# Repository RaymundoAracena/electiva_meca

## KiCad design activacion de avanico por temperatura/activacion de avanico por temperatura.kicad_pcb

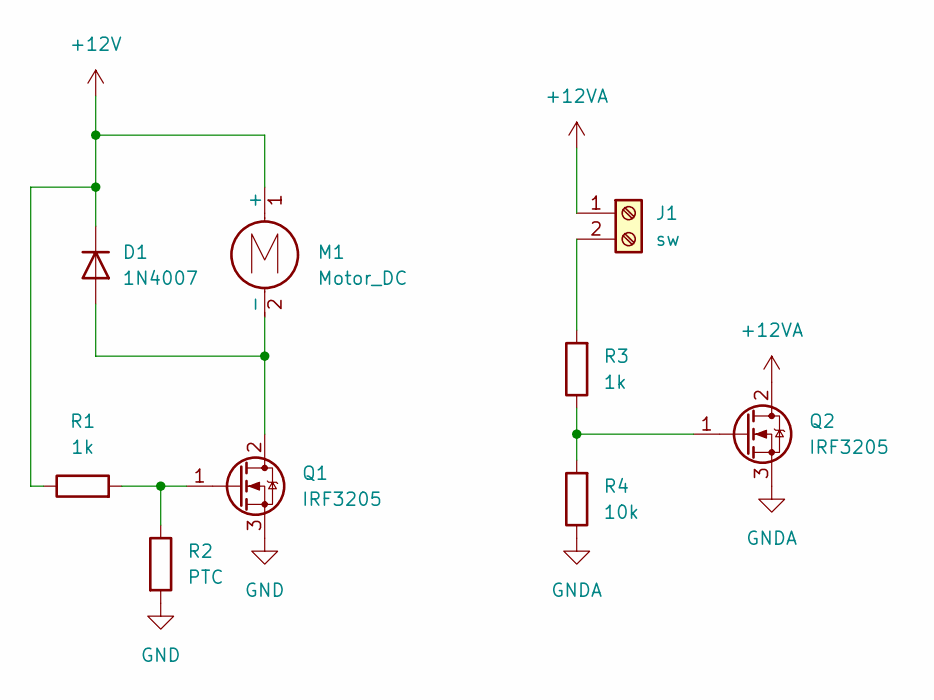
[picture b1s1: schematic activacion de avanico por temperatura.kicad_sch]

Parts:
D1: 1N4007; D_DO-41_SOD81_P10.16mm_Horizontal
J1: sw; PinHeader_1x02_P2.54mm_Vertical
M1: Motor_DC; PinHeader_1x02_P2.54mm_Vertical
Q1, Q2: IRF3205; TO-220-3_Vertical
R1, R3: 1k; R_Axial_DIN0207_L6.3mm_D2.5mm_P7.62mm_Horizontal
R2: PTC; R_Axial_DIN0204_L3.6mm_D1.6mm_P5.08mm_Horizontal
R4: 10k; R_Axial_DIN0207_L6.3mm_D2.5mm_P7.62mm_Horizontal

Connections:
+12V: D1.1 (K), M1.1 (+), R1.1
+12VA: J1.1, Q2.2 (D)
GND: Q1.3 (S), R2.2
GNDA: Q2.3 (S), R4.1
unnamed: D1.2 (A), M1.2 (-), Q1.2 (D)
unnamed: J1.2, R3.2
unnamed: Q1.1 (G), R1.2, R2.1
unnamed: Q2.1 (G), R3.1, R4.2

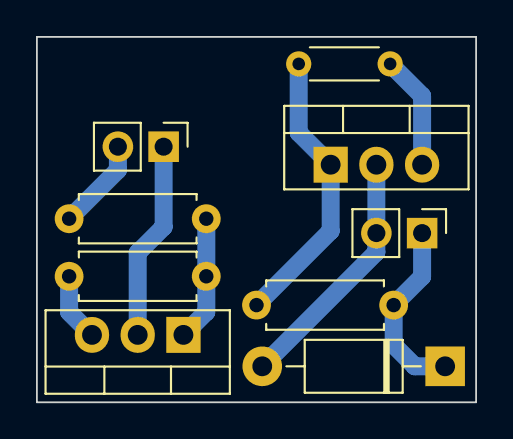
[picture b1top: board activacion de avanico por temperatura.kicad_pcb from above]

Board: 2 copper layers, 24.4 x 20.3 mm, 9 parts (0 on the bottom side), 8 nets.

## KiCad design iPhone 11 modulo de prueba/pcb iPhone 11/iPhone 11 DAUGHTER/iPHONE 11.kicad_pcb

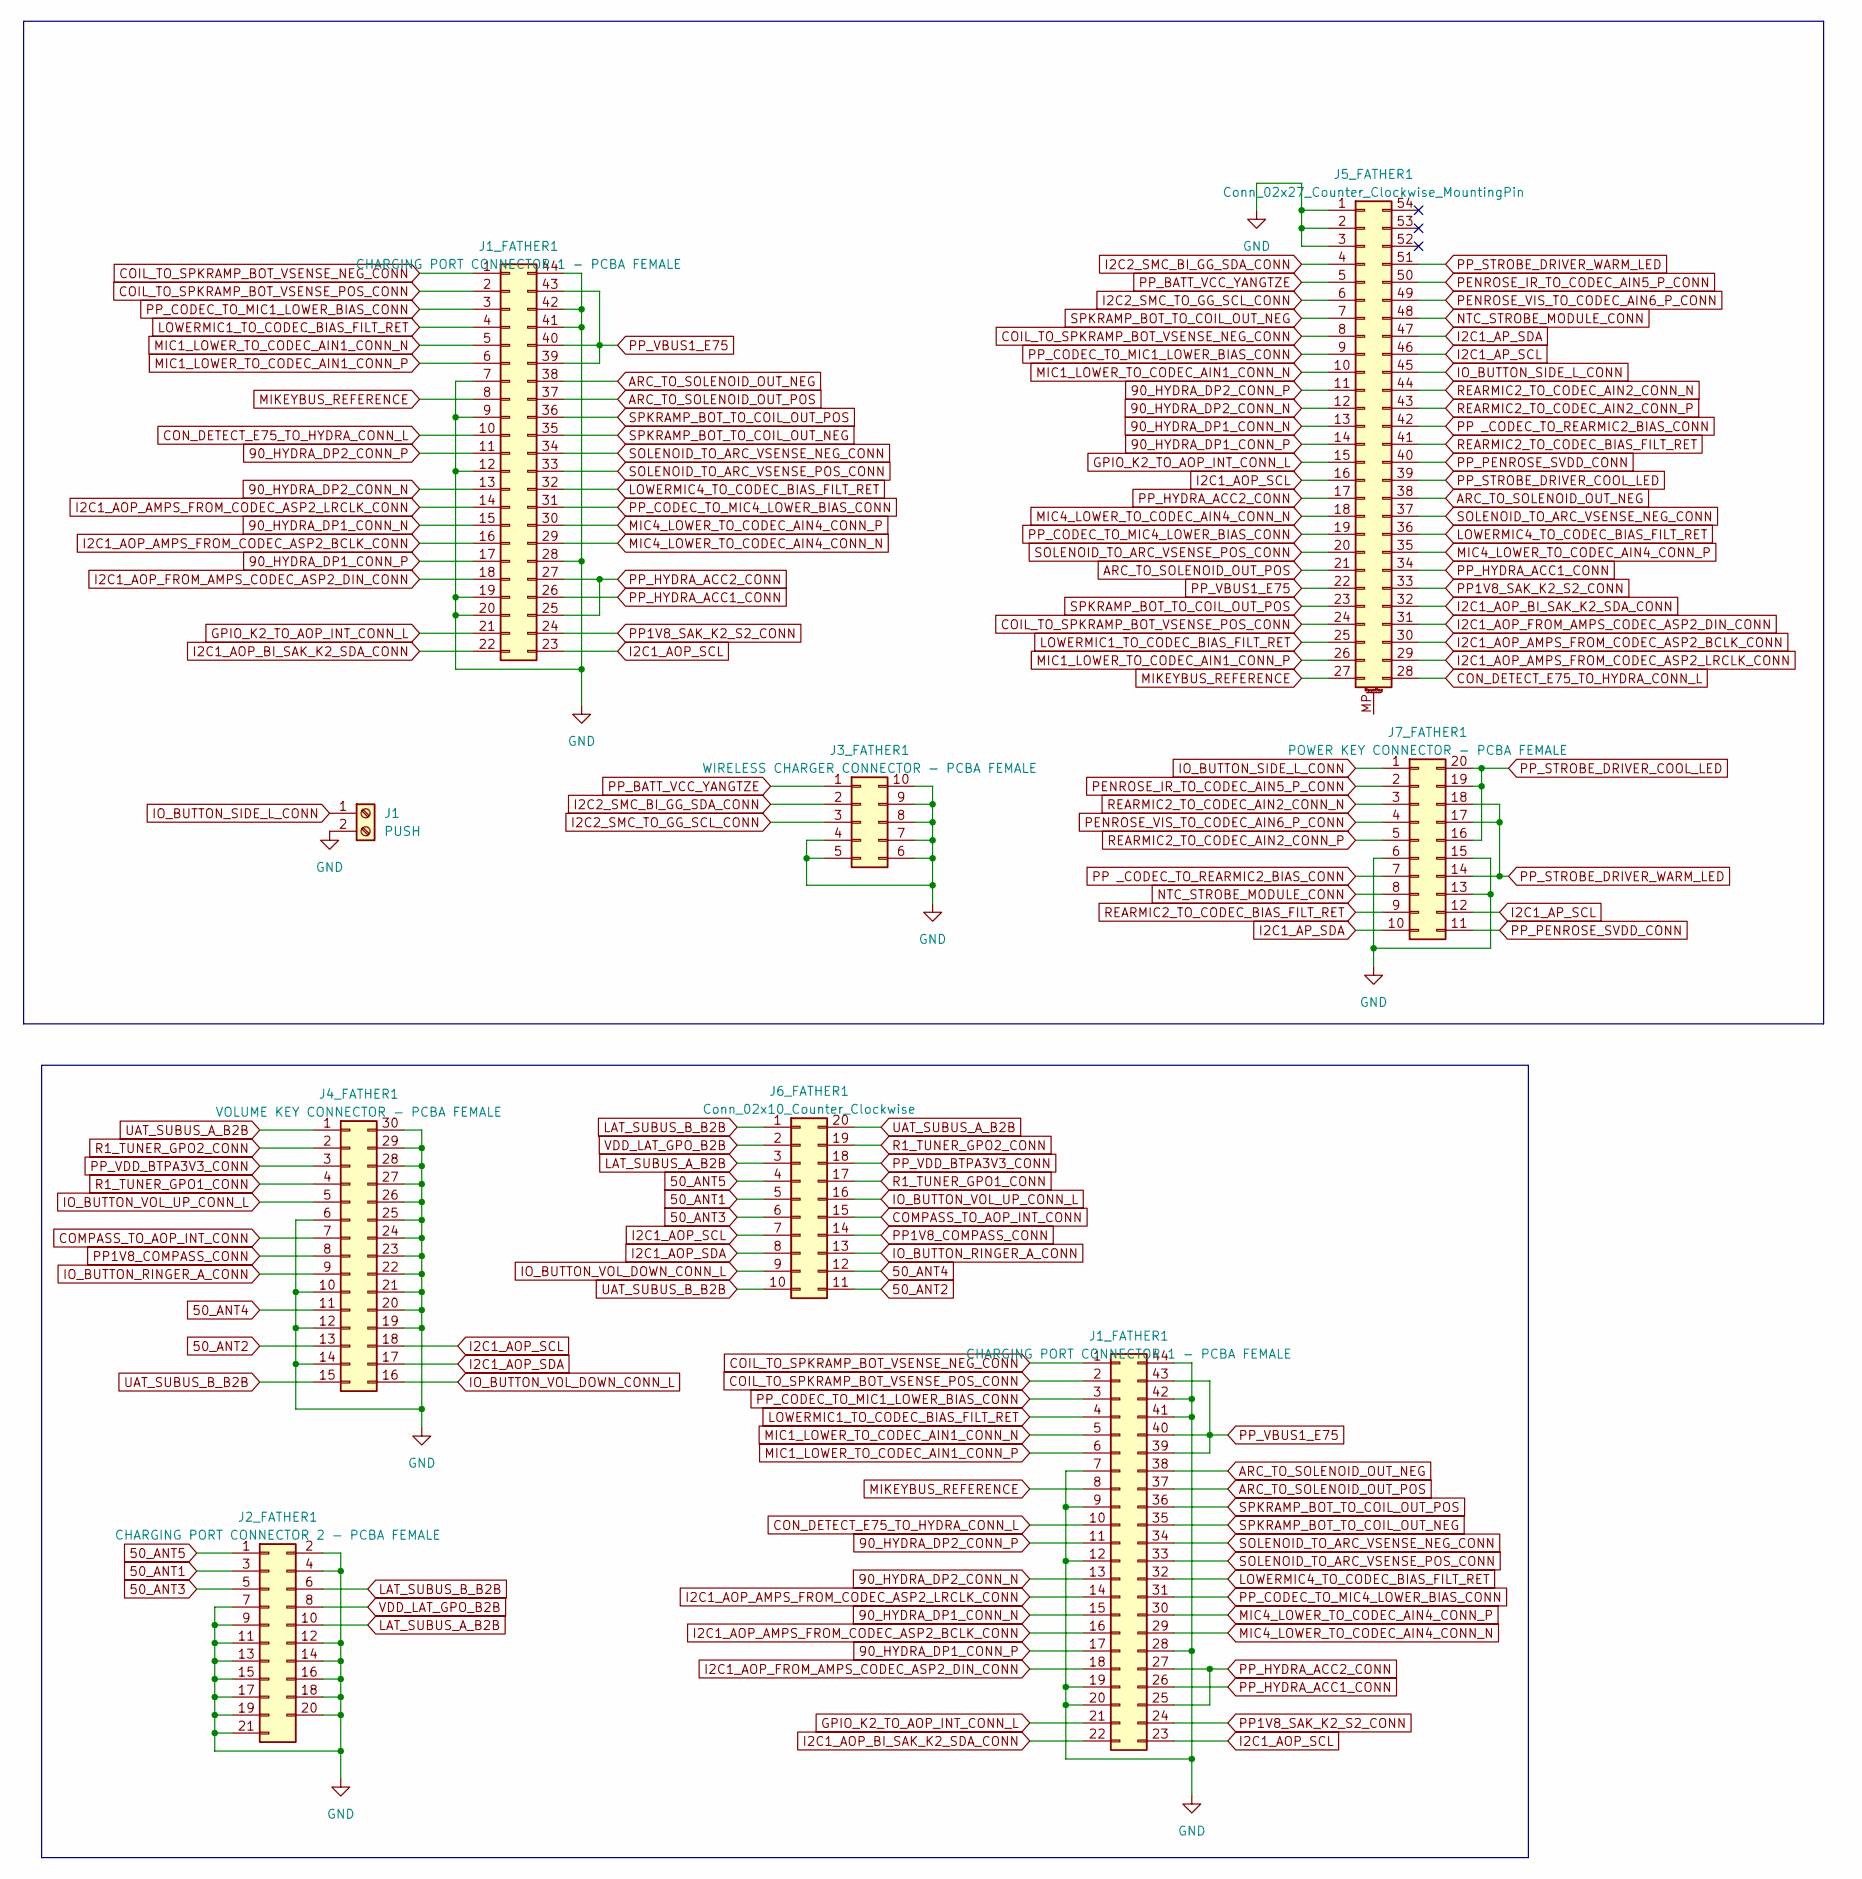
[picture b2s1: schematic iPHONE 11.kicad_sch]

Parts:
J1: PUSH; PinHeader_1x02_P2.54mm_Horizontal
J1_FATHER1: CHARGING PORT CONNECTOR 1 - PCBA FEMALE; IP11_J8200_13_PCBA_CHARGING_CONNECTOR_1
J2_FATHER1: CHARGING PORT CONNECTOR 2 - PCBA FEMALE; IP11_J-LAT-K_14_PCBA_CHARGING_CONNECTOR_2
J3_FATHER1: WIRELESS CHARGER CONNECTOR - PCBA FEMALE; IP11_J7100_7_PCBA_WIRELESS_CHARGER_CONNECTOR
J4_FATHER1: VOLUME KEY CONNECTOR - PCBA FEMALE; IP11_J-UAT-K_1_PCBA_VOLUME_KEY_CONNECTOR
J5_FATHER1: Conn_02x27_Counter_Clockwise_MountingPin; ZIF 54pin
J6_FATHER1: Conn_02x10_Counter_Clockwise; ZIF 20pin
J7_FATHER1: POWER KEY CONNECTOR - PCBA FEMALE; IP11_J7700_9_PCBA_POWER_KEY_FLEX_CONNECTOR

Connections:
50_ANT1: J2_FATHER1.3, J6_FATHER1.5
50_ANT2: J4_FATHER1.13, J6_FATHER1.11
50_ANT3: J2_FATHER1.5, J6_FATHER1.6
50_ANT4: J4_FATHER1.11, J6_FATHER1.12
50_ANT5: J2_FATHER1.1, J6_FATHER1.4
90_HYDRA_DP1_CONN_N: J1_FATHER1.15, J5_FATHER1.13; also elsewhere on the board
90_HYDRA_DP1_CONN_P: J1_FATHER1.17, J5_FATHER1.14; also elsewhere on the board
90_HYDRA_DP2_CONN_N: J1_FATHER1.13, J5_FATHER1.12; also elsewhere on the board
90_HYDRA_DP2_CONN_P: J1_FATHER1.11, J5_FATHER1.11; also elsewhere on the board
ARC_TO_SOLENOID_OUT_NEG: J1_FATHER1.38, J5_FATHER1.38; also elsewhere on the board
ARC_TO_SOLENOID_OUT_POS: J1_FATHER1.37, J5_FATHER1.21; also elsewhere on the board
COIL_TO_SPKRAMP_BOT_VSENSE_NEG_CONN: J1_FATHER1.1, J5_FATHER1.8; also elsewhere on the board
COIL_TO_SPKRAMP_BOT_VSENSE_POS_CONN: J1_FATHER1.2, J5_FATHER1.24; also elsewhere on the board
COMPASS_TO_AOP_INT_CONN: J4_FATHER1.7, J6_FATHER1.15
CON_DETECT_E75_TO_HYDRA_CONN_L: J1_FATHER1.10, J5_FATHER1.28; also elsewhere on the board
GND: J1.2, J1_FATHER1.7, J1_FATHER1.9, J1_FATHER1.12, J1_FATHER1.19, J1_FATHER1.20, J1_FATHER1.28, J1_FATHER1.41, J1_FATHER1.42, J1_FATHER1.44, J2_FATHER1.2, J2_FATHER1.4, J2_FATHER1.7, J2_FATHER1.9, J2_FATHER1.11, J2_FATHER1.12, J2_FATHER1.13, J2_FATHER1.14, J2_FATHER1.15, J2_FATHER1.16, J2_FATHER1.17, J2_FATHER1.18, J2_FATHER1.19, J2_FATHER1.20, J2_FATHER1.21, J3_FATHER1.4, J3_FATHER1.5, J3_FATHER1.6, J3_FATHER1.7, J3_FATHER1.8, J3_FATHER1.9, J3_FATHER1.10, J4_FATHER1.6, J4_FATHER1.10, J4_FATHER1.12, J4_FATHER1.14, J4_FATHER1.19, J4_FATHER1.20, J4_FATHER1.21, J4_FATHER1.22, J4_FATHER1.23, J4_FATHER1.24, J4_FATHER1.25, J4_FATHER1.26, J4_FATHER1.27, J4_FATHER1.28, J4_FATHER1.29, J4_FATHER1.30, J5_FATHER1.1, J5_FATHER1.2, J5_FATHER1.3, J7_FATHER1.6, J7_FATHER1.13, J7_FATHER1.15; also elsewhere on the board
GPIO_K2_TO_AOP_INT_CONN_L: J1_FATHER1.21, J5_FATHER1.15; also elsewhere on the board
I2C1_AOP_AMPS_FROM_CODEC_ASP2_BCLK_CONN: J1_FATHER1.16, J5_FATHER1.30; also elsewhere on the board
I2C1_AOP_AMPS_FROM_CODEC_ASP2_LRCLK_CONN: J1_FATHER1.14, J5_FATHER1.29; also elsewhere on the board
I2C1_AOP_BI_SAK_K2_SDA_CONN: J1_FATHER1.22, J5_FATHER1.32; also elsewhere on the board
I2C1_AOP_FROM_AMPS_CODEC_ASP2_DIN_CONN: J1_FATHER1.18, J5_FATHER1.31; also elsewhere on the board
I2C1_AOP_SCL: J1_FATHER1.23, J4_FATHER1.18, J5_FATHER1.16, J6_FATHER1.7; also elsewhere on the board
I2C1_AOP_SDA: J4_FATHER1.17, J6_FATHER1.8
I2C1_AP_SCL: J5_FATHER1.46, J7_FATHER1.12
I2C1_AP_SDA: J5_FATHER1.47, J7_FATHER1.10
I2C2_SMC_BI_GG_SDA_CONN: J3_FATHER1.2, J5_FATHER1.4
I2C2_SMC_TO_GG_SCL_CONN: J3_FATHER1.3, J5_FATHER1.6
IO_BUTTON_RINGER_A_CONN: J4_FATHER1.9, J6_FATHER1.13
IO_BUTTON_SIDE_L_CONN: J1.1, J5_FATHER1.45, J7_FATHER1.1
IO_BUTTON_VOL_DOWN_CONN_L: J4_FATHER1.16, J6_FATHER1.9
IO_BUTTON_VOL_UP_CONN_L: J4_FATHER1.5, J6_FATHER1.16
LAT_SUBUS_A_B2B: J2_FATHER1.10, J6_FATHER1.3
LAT_SUBUS_B_B2B: J2_FATHER1.6, J6_FATHER1.1
LOWERMIC1_TO_CODEC_BIAS_FILT_RET: J1_FATHER1.4, J5_FATHER1.25; also elsewhere on the board
LOWERMIC4_TO_CODEC_BIAS_FILT_RET: J1_FATHER1.32, J5_FATHER1.36; also elsewhere on the board
MIC1_LOWER_TO_CODEC_AIN1_CONN_N: J1_FATHER1.5, J5_FATHER1.10; also elsewhere on the board
MIC1_LOWER_TO_CODEC_AIN1_CONN_P: J1_FATHER1.6, J5_FATHER1.26; also elsewhere on the board
MIC4_LOWER_TO_CODEC_AIN4_CONN_N: J1_FATHER1.29, J5_FATHER1.18; also elsewhere on the board
MIC4_LOWER_TO_CODEC_AIN4_CONN_P: J1_FATHER1.30, J5_FATHER1.35; also elsewhere on the board
MIKEYBUS_REFERENCE: J1_FATHER1.8, J5_FATHER1.27; also elsewhere on the board
NTC_STROBE_MODULE_CONN: J5_FATHER1.48, J7_FATHER1.8
PENROSE_IR_TO_CODEC_AIN5_P_CONN: J5_FATHER1.50, J7_FATHER1.2
PENROSE_VIS_TO_CODEC_AIN6_P_CONN: J5_FATHER1.49, J7_FATHER1.4
PP1V8_COMPASS_CONN: J4_FATHER1.8, J6_FATHER1.14
PP1V8_SAK_K2_S2_CONN: J1_FATHER1.24, J5_FATHER1.33; also elsewhere on the board
PP _CODEC_TO_REARMIC2_BIAS_CONN: J5_FATHER1.42, J7_FATHER1.7
PP_BATT_VCC_YANGTZE: J3_FATHER1.1, J5_FATHER1.5
PP_CODEC_TO_MIC1_LOWER_BIAS_CONN: J1_FATHER1.3, J5_FATHER1.9; also elsewhere on the board
PP_CODEC_TO_MIC4_LOWER_BIAS_CONN: J1_FATHER1.31, J5_FATHER1.19; also elsewhere on the board
PP_HYDRA_ACC1_CONN: J1_FATHER1.26, J5_FATHER1.34; also elsewhere on the board
PP_HYDRA_ACC2_CONN: J1_FATHER1.25, J1_FATHER1.27, J5_FATHER1.17; also elsewhere on the board
PP_PENROSE_SVDD_CONN: J5_FATHER1.40, J7_FATHER1.11
PP_STROBE_DRIVER_COOL_LED: J5_FATHER1.39, J7_FATHER1.16, J7_FATHER1.19, J7_FATHER1.20
PP_STROBE_DRIVER_WARM_LED: J5_FATHER1.51, J7_FATHER1.14, J7_FATHER1.17, J7_FATHER1.18
PP_VBUS1_E75: J1_FATHER1.39, J1_FATHER1.40, J1_FATHER1.43, J5_FATHER1.22; also elsewhere on the board
PP_VDD_BTPA3V3_CONN: J4_FATHER1.3, J6_FATHER1.18
R1_TUNER_GPO1_CONN: J4_FATHER1.4, J6_FATHER1.17
R1_TUNER_GPO2_CONN: J4_FATHER1.2, J6_FATHER1.19
REARMIC2_TO_CODEC_AIN2_CONN_N: J5_FATHER1.44, J7_FATHER1.3
REARMIC2_TO_CODEC_AIN2_CONN_P: J5_FATHER1.43, J7_FATHER1.5
REARMIC2_TO_CODEC_BIAS_FILT_RET: J5_FATHER1.41, J7_FATHER1.9
SOLENOID_TO_ARC_VSENSE_NEG_CONN: J1_FATHER1.34, J5_FATHER1.37; also elsewhere on the board
SOLENOID_TO_ARC_VSENSE_POS_CONN: J1_FATHER1.33, J5_FATHER1.20; also elsewhere on the board
SPKRAMP_BOT_TO_COIL_OUT_NEG: J1_FATHER1.35, J5_FATHER1.7; also elsewhere on the board
SPKRAMP_BOT_TO_COIL_OUT_POS: J1_FATHER1.36, J5_FATHER1.23; also elsewhere on the board
UAT_SUBUS_A_B2B: J4_FATHER1.1, J6_FATHER1.20
UAT_SUBUS_B_B2B: J4_FATHER1.15, J6_FATHER1.10
VDD_LAT_GPO_B2B: J2_FATHER1.8, J6_FATHER1.2

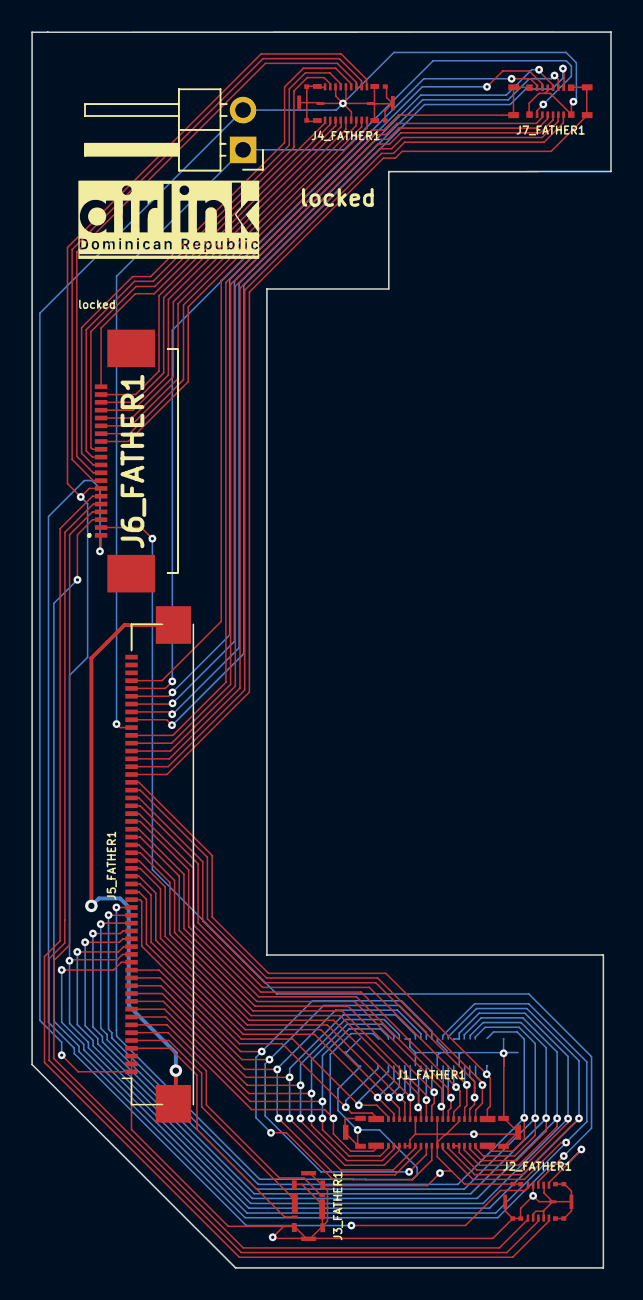
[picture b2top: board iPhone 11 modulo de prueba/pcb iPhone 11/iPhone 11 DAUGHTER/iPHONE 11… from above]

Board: 2 copper layers, 37.0 x 79.0 mm, 9 parts (1 on the bottom side), 68 nets.

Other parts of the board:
J1_FATHER2: CHARGING PORT CONNECTOR 1 - PCBA FEMALE; IP11_J8200_13_PCBA_CHARGING_CONNECTOR_1

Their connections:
90_HYDRA_DP1_CONN_N: J1_FATHER2.15; also elsewhere on the board
90_HYDRA_DP1_CONN_P: J1_FATHER2.17; also elsewhere on the board
90_HYDRA_DP2_CONN_N: J1_FATHER2.13; also elsewhere on the board
90_HYDRA_DP2_CONN_P: J1_FATHER2.11; also elsewhere on the board
ARC_TO_SOLENOID_OUT_NEG: J1_FATHER2.38; also elsewhere on the board
ARC_TO_SOLENOID_OUT_POS: J1_FATHER2.37; also elsewhere on the board
COIL_TO_SPKRAMP_BOT_VSENSE_NEG_CONN: J1_FATHER2.1; also elsewhere on the board
COIL_TO_SPKRAMP_BOT_VSENSE_POS_CONN: J1_FATHER2.2; also elsewhere on the board
CON_DETECT_E75_TO_HYDRA_CONN_L: J1_FATHER2.10; also elsewhere on the board
GND: J1_FATHER2.7, J1_FATHER2.9, J1_FATHER2.12, J1_FATHER2.19, J1_FATHER2.20, J1_FATHER2.28, J1_FATHER2.41, J1_FATHER2.42, J1_FATHER2.44; also elsewhere on the board
GPIO_K2_TO_AOP_INT_CONN_L: J1_FATHER2.21; also elsewhere on the board
I2C1_AOP_AMPS_FROM_CODEC_ASP2_BCLK_CONN: J1_FATHER2.16; also elsewhere on the board
I2C1_AOP_AMPS_FROM_CODEC_ASP2_LRCLK_CONN: J1_FATHER2.14; also elsewhere on the board
I2C1_AOP_BI_SAK_K2_SDA_CONN: J1_FATHER2.22; also elsewhere on the board
I2C1_AOP_FROM_AMPS_CODEC_ASP2_DIN_CONN: J1_FATHER2.18; also elsewhere on the board
I2C1_AOP_SCL: J1_FATHER2.23; also elsewhere on the board
LOWERMIC1_TO_CODEC_BIAS_FILT_RET: J1_FATHER2.4; also elsewhere on the board
LOWERMIC4_TO_CODEC_BIAS_FILT_RET: J1_FATHER2.32; also elsewhere on the board
MIC1_LOWER_TO_CODEC_AIN1_CONN_N: J1_FATHER2.5; also elsewhere on the board
MIC1_LOWER_TO_CODEC_AIN1_CONN_P: J1_FATHER2.6; also elsewhere on the board
MIC4_LOWER_TO_CODEC_AIN4_CONN_N: J1_FATHER2.29; also elsewhere on the board
MIC4_LOWER_TO_CODEC_AIN4_CONN_P: J1_FATHER2.30; also elsewhere on the board
MIKEYBUS_REFERENCE: J1_FATHER2.8; also elsewhere on the board
PP1V8_SAK_K2_S2_CONN: J1_FATHER2.24; also elsewhere on the board
PP_CODEC_TO_MIC1_LOWER_BIAS_CONN: J1_FATHER2.3; also elsewhere on the board
PP_CODEC_TO_MIC4_LOWER_BIAS_CONN: J1_FATHER2.31; also elsewhere on the board
PP_HYDRA_ACC1_CONN: J1_FATHER2.26; also elsewhere on the board
PP_HYDRA_ACC2_CONN: J1_FATHER2.25, J1_FATHER2.27; also elsewhere on the board
PP_VBUS1_E75: J1_FATHER2.39, J1_FATHER2.40, J1_FATHER2.43; also elsewhere on the board
SOLENOID_TO_ARC_VSENSE_NEG_CONN: J1_FATHER2.34; also elsewhere on the board
SOLENOID_TO_ARC_VSENSE_POS_CONN: J1_FATHER2.33; also elsewhere on the board
SPKRAMP_BOT_TO_COIL_OUT_NEG: J1_FATHER2.35; also elsewhere on the board
SPKRAMP_BOT_TO_COIL_OUT_POS: J1_FATHER2.36; also elsewhere on the board

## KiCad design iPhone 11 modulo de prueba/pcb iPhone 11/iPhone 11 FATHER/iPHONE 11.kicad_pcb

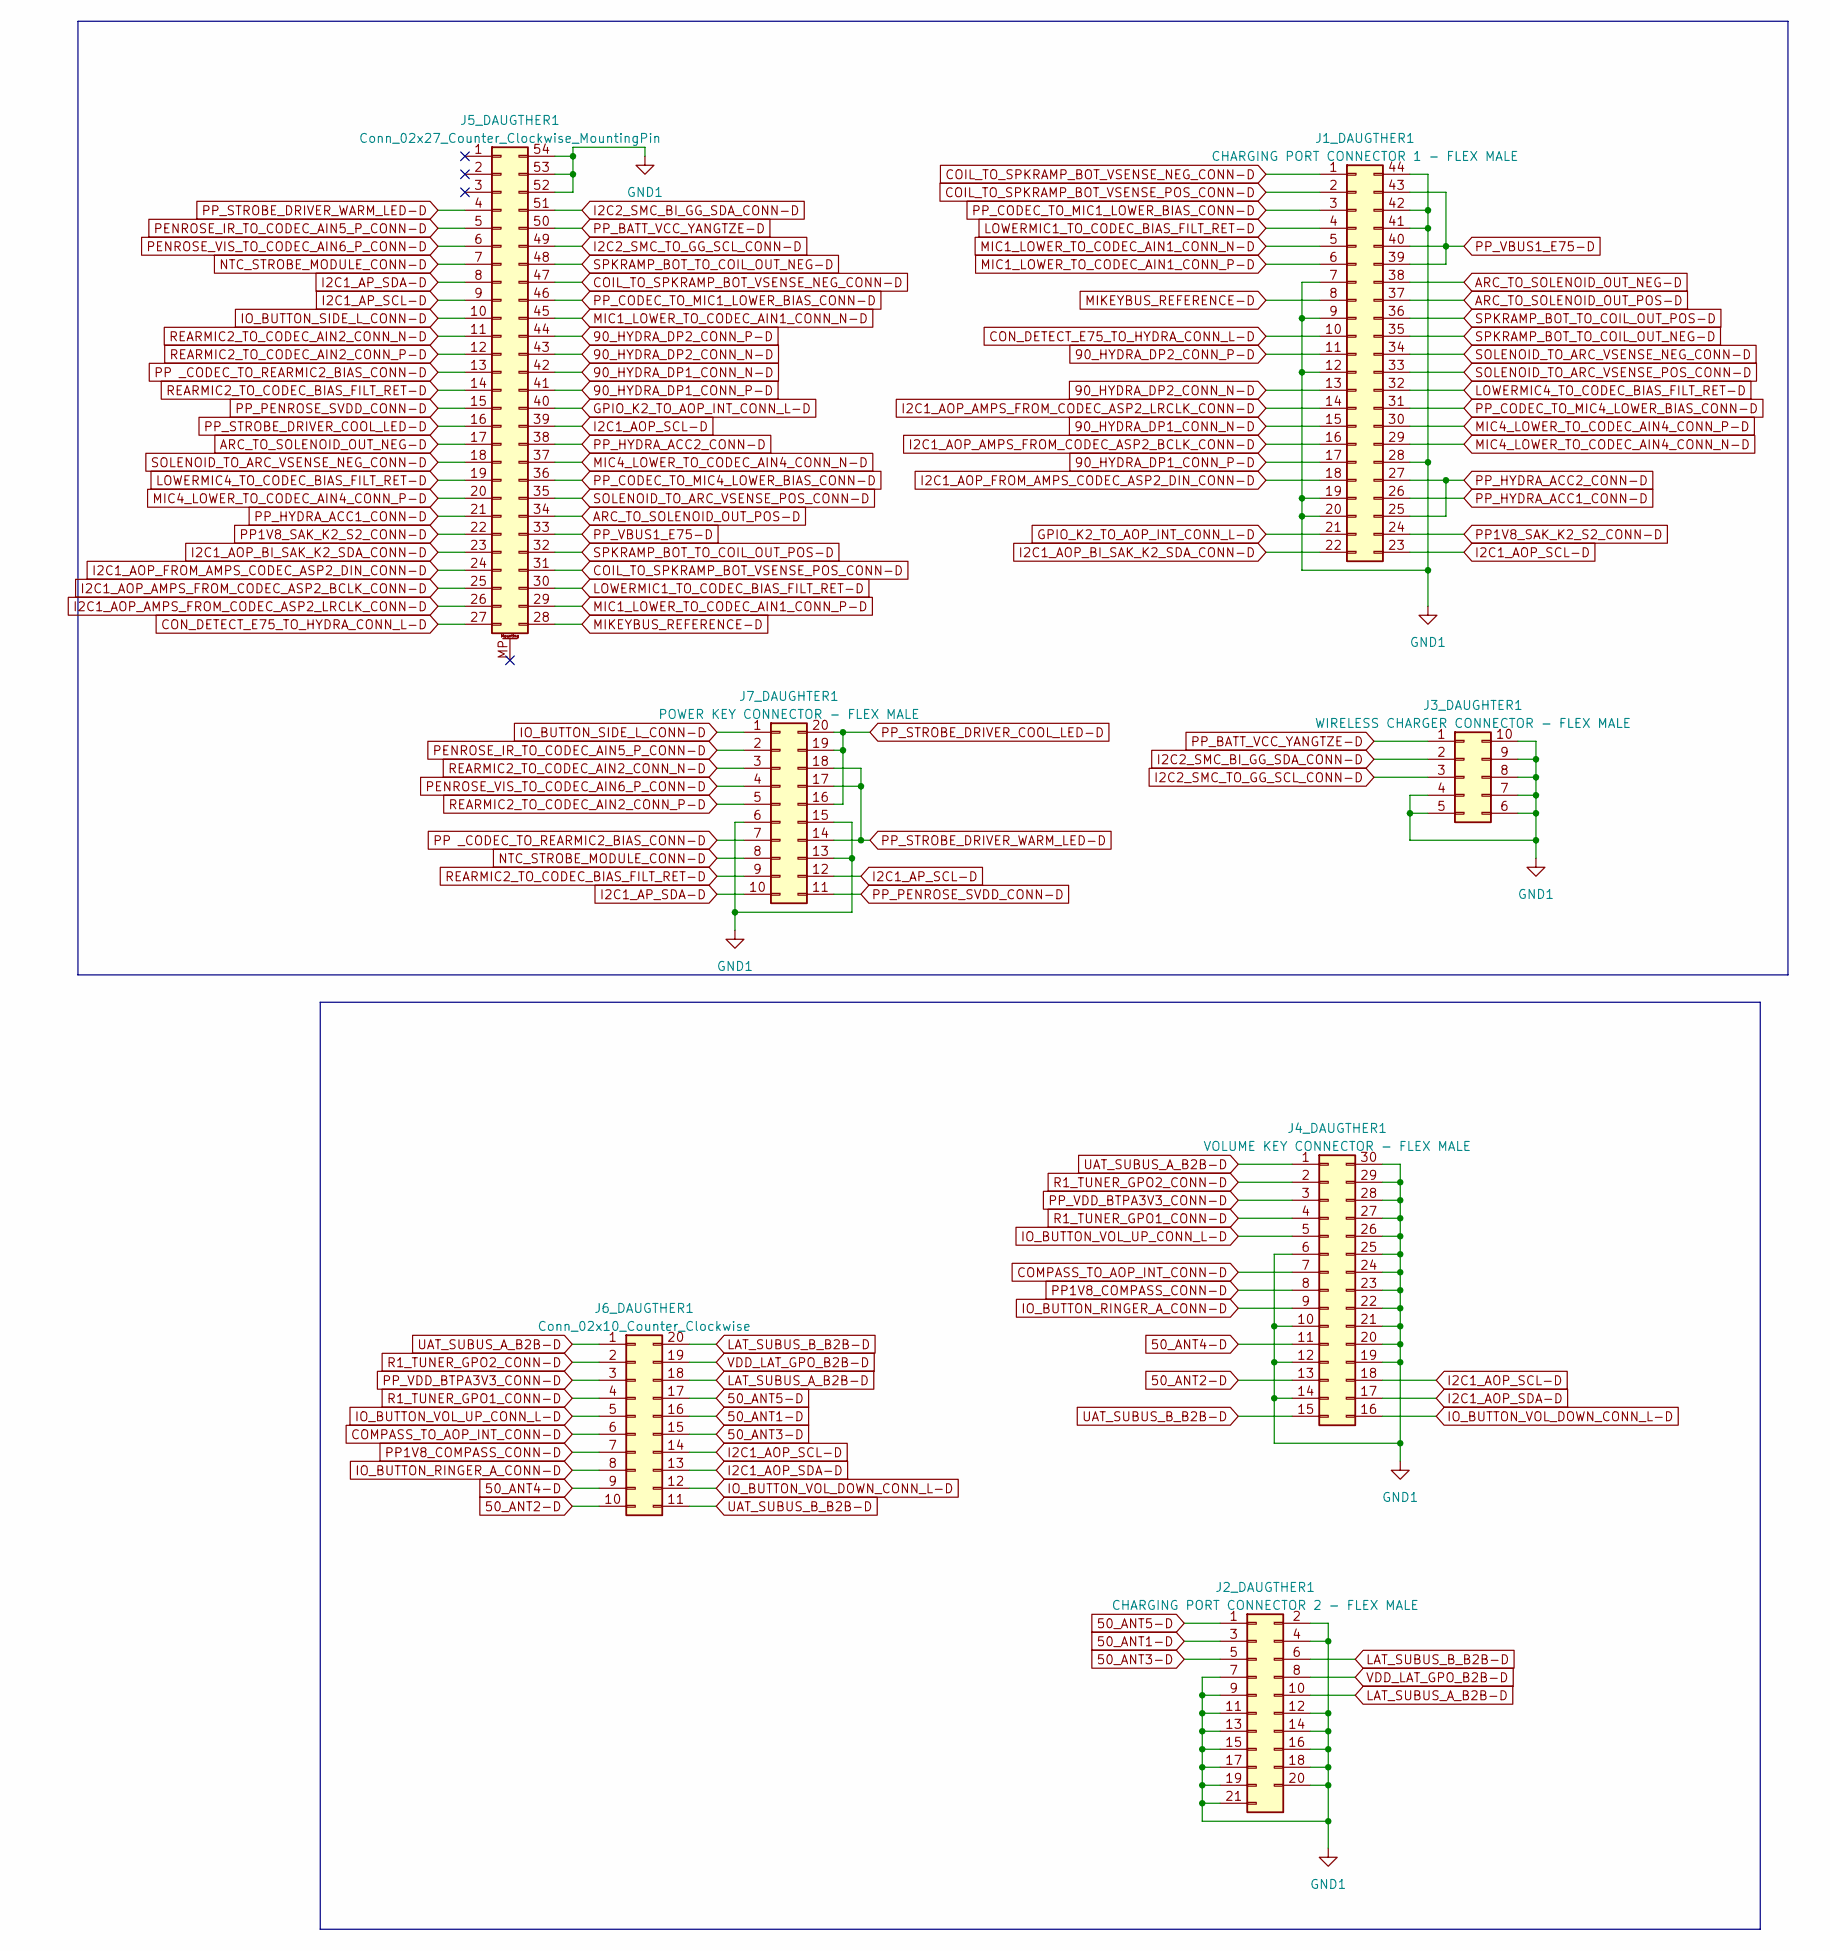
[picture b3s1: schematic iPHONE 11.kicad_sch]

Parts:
J1_DAUGTHER1: CHARGING PORT CONNECTOR 1 - FLEX MALE; IP11_J8200_13_PCBA_CHARGING_CONNECTOR_1
J2_DAUGTHER1: CHARGING PORT CONNECTOR 2 - FLEX MALE; IP11_J-LAT-K_14_PCBA_CHARGING_CONNECTOR_2
J3_DAUGHTER1: WIRELESS CHARGER CONNECTOR - FLEX MALE; IP11_J7100_7_PCBA_WIRELESS_CHARGER_CONNECTOR
J4_DAUGTHER1: VOLUME KEY CONNECTOR - FLEX MALE; IP11_J-UAT-K_1_PCBA_VOLUME_KEY_CONNECTOR
J5_DAUGTHER1: Conn_02x27_Counter_Clockwise_MountingPin; ZIF 54pin
J6_DAUGTHER1: Conn_02x10_Counter_Clockwise; ZIF 20pin
J7_DAUGHTER1: POWER KEY CONNECTOR - FLEX MALE; IP11_J7700_9_PCBA_POWER_KEY_FLEX_CONNECTOR

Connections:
50_ANT1-D: J2_DAUGTHER1.3, J6_DAUGTHER1.16
50_ANT2-D: J4_DAUGTHER1.13, J6_DAUGTHER1.10
50_ANT3-D: J2_DAUGTHER1.5, J6_DAUGTHER1.15
50_ANT4-D: J4_DAUGTHER1.11, J6_DAUGTHER1.9
50_ANT5-D: J2_DAUGTHER1.1, J6_DAUGTHER1.17
90_HYDRA_DP1_CONN_N-D: J1_DAUGTHER1.15, J5_DAUGTHER1.42
90_HYDRA_DP1_CONN_P-D: J1_DAUGTHER1.17, J5_DAUGTHER1.41
90_HYDRA_DP2_CONN_N-D: J1_DAUGTHER1.13, J5_DAUGTHER1.43
90_HYDRA_DP2_CONN_P-D: J1_DAUGTHER1.11, J5_DAUGTHER1.44
ARC_TO_SOLENOID_OUT_NEG-D: J1_DAUGTHER1.38, J5_DAUGTHER1.17
ARC_TO_SOLENOID_OUT_POS-D: J1_DAUGTHER1.37, J5_DAUGTHER1.34
COIL_TO_SPKRAMP_BOT_VSENSE_NEG_CONN-D: J1_DAUGTHER1.1, J5_DAUGTHER1.47
COIL_TO_SPKRAMP_BOT_VSENSE_POS_CONN-D: J1_DAUGTHER1.2, J5_DAUGTHER1.31
COMPASS_TO_AOP_INT_CONN-D: J4_DAUGTHER1.7, J6_DAUGTHER1.6
CON_DETECT_E75_TO_HYDRA_CONN_L-D: J1_DAUGTHER1.10, J5_DAUGTHER1.27
GND1: J1_DAUGTHER1.7, J1_DAUGTHER1.9, J1_DAUGTHER1.12, J1_DAUGTHER1.19, J1_DAUGTHER1.20, J1_DAUGTHER1.28, J1_DAUGTHER1.41, J1_DAUGTHER1.42, J1_DAUGTHER1.44, J2_DAUGTHER1.2, J2_DAUGTHER1.4, J2_DAUGTHER1.7, J2_DAUGTHER1.9, J2_DAUGTHER1.11, J2_DAUGTHER1.12, J2_DAUGTHER1.13, J2_DAUGTHER1.14, J2_DAUGTHER1.15, J2_DAUGTHER1.16, J2_DAUGTHER1.17, J2_DAUGTHER1.18, J2_DAUGTHER1.19, J2_DAUGTHER1.20, J2_DAUGTHER1.21, J3_DAUGHTER1.4, J3_DAUGHTER1.5, J3_DAUGHTER1.6, J3_DAUGHTER1.7, J3_DAUGHTER1.8, J3_DAUGHTER1.9, J3_DAUGHTER1.10, J4_DAUGTHER1.6, J4_DAUGTHER1.10, J4_DAUGTHER1.12, J4_DAUGTHER1.14, J4_DAUGTHER1.19, J4_DAUGTHER1.20, J4_DAUGTHER1.21, J4_DAUGTHER1.22, J4_DAUGTHER1.23, J4_DAUGTHER1.24, J4_DAUGTHER1.25, J4_DAUGTHER1.26, J4_DAUGTHER1.27, J4_DAUGTHER1.28, J4_DAUGTHER1.29, J4_DAUGTHER1.30, J5_DAUGTHER1.52, J5_DAUGTHER1.53, J5_DAUGTHER1.54, J7_DAUGHTER1.6, J7_DAUGHTER1.13, J7_DAUGHTER1.15
GPIO_K2_TO_AOP_INT_CONN_L-D: J1_DAUGTHER1.21, J5_DAUGTHER1.40
I2C1_AOP_AMPS_FROM_CODEC_ASP2_BCLK_CONN-D: J1_DAUGTHER1.16, J5_DAUGTHER1.25
I2C1_AOP_AMPS_FROM_CODEC_ASP2_LRCLK_CONN-D: J1_DAUGTHER1.14, J5_DAUGTHER1.26
I2C1_AOP_BI_SAK_K2_SDA_CONN-D: J1_DAUGTHER1.22, J5_DAUGTHER1.23
I2C1_AOP_FROM_AMPS_CODEC_ASP2_DIN_CONN-D: J1_DAUGTHER1.18, J5_DAUGTHER1.24
I2C1_AOP_SCL-D: J1_DAUGTHER1.23, J4_DAUGTHER1.18, J5_DAUGTHER1.39, J6_DAUGTHER1.14
I2C1_AOP_SDA-D: J4_DAUGTHER1.17, J6_DAUGTHER1.13
I2C1_AP_SCL-D: J5_DAUGTHER1.9, J7_DAUGHTER1.12
I2C1_AP_SDA-D: J5_DAUGTHER1.8, J7_DAUGHTER1.10
I2C2_SMC_BI_GG_SDA_CONN-D: J3_DAUGHTER1.2, J5_DAUGTHER1.51
I2C2_SMC_TO_GG_SCL_CONN-D: J3_DAUGHTER1.3, J5_DAUGTHER1.49
IO_BUTTON_RINGER_A_CONN-D: J4_DAUGTHER1.9, J6_DAUGTHER1.8
IO_BUTTON_SIDE_L_CONN-D: J5_DAUGTHER1.10, J7_DAUGHTER1.1
IO_BUTTON_VOL_DOWN_CONN_L-D: J4_DAUGTHER1.16, J6_DAUGTHER1.12
IO_BUTTON_VOL_UP_CONN_L-D: J4_DAUGTHER1.5, J6_DAUGTHER1.5
LAT_SUBUS_A_B2B-D: J2_DAUGTHER1.10, J6_DAUGTHER1.18
LAT_SUBUS_B_B2B-D: J2_DAUGTHER1.6, J6_DAUGTHER1.20
LOWERMIC1_TO_CODEC_BIAS_FILT_RET-D: J1_DAUGTHER1.4, J5_DAUGTHER1.30
LOWERMIC4_TO_CODEC_BIAS_FILT_RET-D: J1_DAUGTHER1.32, J5_DAUGTHER1.19
MIC1_LOWER_TO_CODEC_AIN1_CONN_N-D: J1_DAUGTHER1.5, J5_DAUGTHER1.45
MIC1_LOWER_TO_CODEC_AIN1_CONN_P-D: J1_DAUGTHER1.6, J5_DAUGTHER1.29
MIC4_LOWER_TO_CODEC_AIN4_CONN_N-D: J1_DAUGTHER1.29, J5_DAUGTHER1.37
MIC4_LOWER_TO_CODEC_AIN4_CONN_P-D: J1_DAUGTHER1.30, J5_DAUGTHER1.20
MIKEYBUS_REFERENCE-D: J1_DAUGTHER1.8, J5_DAUGTHER1.28
NTC_STROBE_MODULE_CONN-D: J5_DAUGTHER1.7, J7_DAUGHTER1.8
PENROSE_IR_TO_CODEC_AIN5_P_CONN-D: J5_DAUGTHER1.5, J7_DAUGHTER1.2
PENROSE_VIS_TO_CODEC_AIN6_P_CONN-D: J5_DAUGTHER1.6, J7_DAUGHTER1.4
PP1V8_COMPASS_CONN-D: J4_DAUGTHER1.8, J6_DAUGTHER1.7
PP1V8_SAK_K2_S2_CONN-D: J1_DAUGTHER1.24, J5_DAUGTHER1.22
PP _CODEC_TO_REARMIC2_BIAS_CONN-D: J5_DAUGTHER1.13, J7_DAUGHTER1.7
PP_BATT_VCC_YANGTZE-D: J3_DAUGHTER1.1, J5_DAUGTHER1.50
PP_CODEC_TO_MIC1_LOWER_BIAS_CONN-D: J1_DAUGTHER1.3, J5_DAUGTHER1.46
PP_CODEC_TO_MIC4_LOWER_BIAS_CONN-D: J1_DAUGTHER1.31, J5_DAUGTHER1.36
PP_HYDRA_ACC1_CONN-D: J1_DAUGTHER1.26, J5_DAUGTHER1.21
PP_HYDRA_ACC2_CONN-D: J1_DAUGTHER1.25, J1_DAUGTHER1.27, J5_DAUGTHER1.38
PP_PENROSE_SVDD_CONN-D: J5_DAUGTHER1.15, J7_DAUGHTER1.11
PP_STROBE_DRIVER_COOL_LED-D: J5_DAUGTHER1.16, J7_DAUGHTER1.16, J7_DAUGHTER1.19, J7_DAUGHTER1.20
PP_STROBE_DRIVER_WARM_LED-D: J5_DAUGTHER1.4, J7_DAUGHTER1.14, J7_DAUGHTER1.17, J7_DAUGHTER1.18
PP_VBUS1_E75-D: J1_DAUGTHER1.39, J1_DAUGTHER1.40, J1_DAUGTHER1.43, J5_DAUGTHER1.33
PP_VDD_BTPA3V3_CONN-D: J4_DAUGTHER1.3, J6_DAUGTHER1.3
R1_TUNER_GPO1_CONN-D: J4_DAUGTHER1.4, J6_DAUGTHER1.4
R1_TUNER_GPO2_CONN-D: J4_DAUGTHER1.2, J6_DAUGTHER1.2
REARMIC2_TO_CODEC_AIN2_CONN_N-D: J5_DAUGTHER1.11, J7_DAUGHTER1.3
REARMIC2_TO_CODEC_AIN2_CONN_P-D: J5_DAUGTHER1.12, J7_DAUGHTER1.5
REARMIC2_TO_CODEC_BIAS_FILT_RET-D: J5_DAUGTHER1.14, J7_DAUGHTER1.9
SOLENOID_TO_ARC_VSENSE_NEG_CONN-D: J1_DAUGTHER1.34, J5_DAUGTHER1.18
SOLENOID_TO_ARC_VSENSE_POS_CONN-D: J1_DAUGTHER1.33, J5_DAUGTHER1.35
SPKRAMP_BOT_TO_COIL_OUT_NEG-D: J1_DAUGTHER1.35, J5_DAUGTHER1.48
SPKRAMP_BOT_TO_COIL_OUT_POS-D: J1_DAUGTHER1.36, J5_DAUGTHER1.32
UAT_SUBUS_A_B2B-D: J4_DAUGTHER1.1, J6_DAUGTHER1.1
UAT_SUBUS_B_B2B-D: J4_DAUGTHER1.15, J6_DAUGTHER1.11
VDD_LAT_GPO_B2B-D: J2_DAUGTHER1.8, J6_DAUGTHER1.19

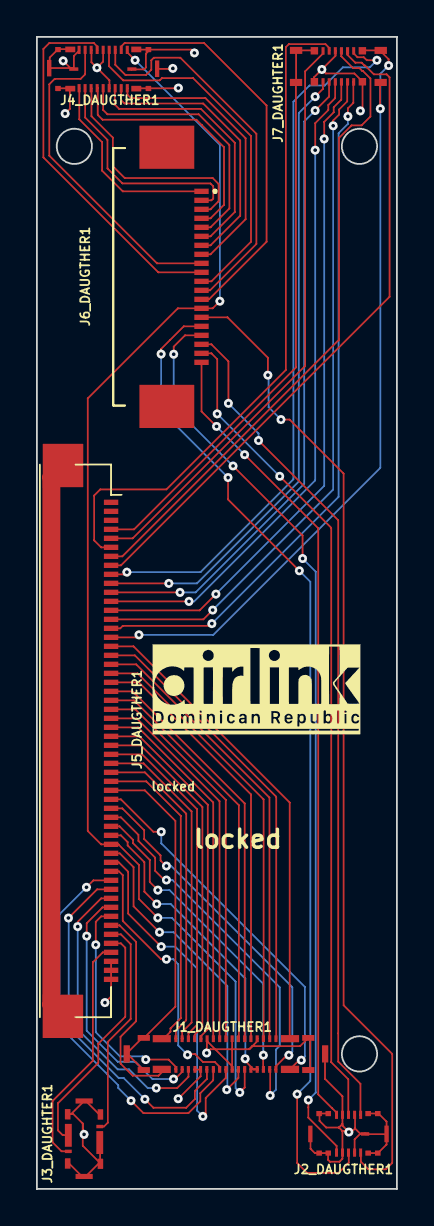
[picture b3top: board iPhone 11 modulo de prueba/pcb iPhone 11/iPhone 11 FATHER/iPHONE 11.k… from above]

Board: 2 copper layers, 20.0 x 64.0 mm, 7 parts (0 on the bottom side), 68 nets.

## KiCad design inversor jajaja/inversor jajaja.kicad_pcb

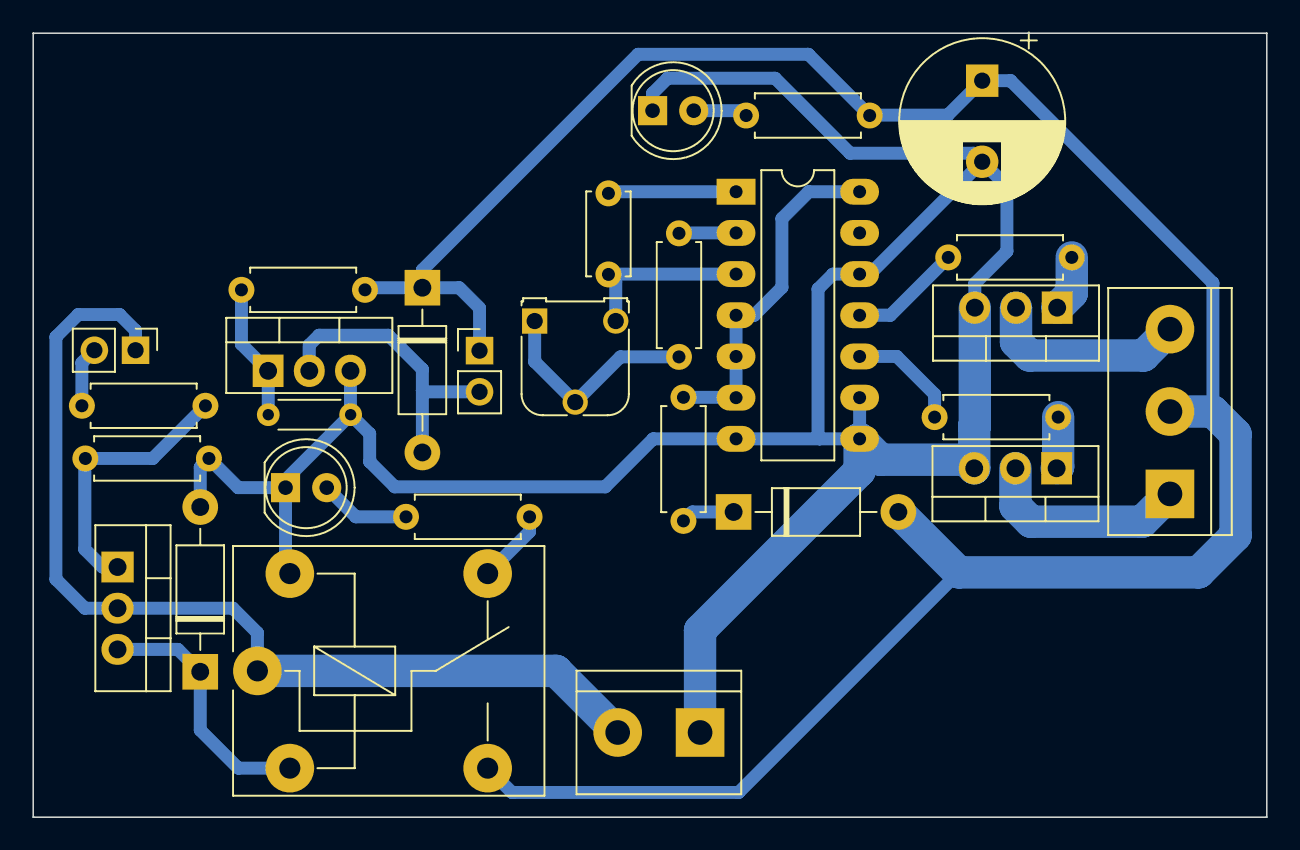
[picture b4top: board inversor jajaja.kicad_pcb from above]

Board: 2 copper layers, 76.1 x 48.4 mm, 28 parts (0 on the bottom side), 23 nets.

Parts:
C2: 2200uF; CP_Radial_D10.0mm_P5.00mm
C3: 0.1uF; C_Disc_D5.0mm_W2.5mm_P5.00mm
D1: on; LED_D5.0mm
D2, D4, D5: 1N4007; D_DO-41_SOD81_P10.16mm_Horizontal
D3: off; LED_D5.0mm
J5: DC; TerminalBlock_bornier-2_P5.08mm
J6: sw; PinHeader_1x02_P2.54mm_Vertical
J7: AC; TerminalBlock_bornier-3_P5.08mm
K1: FINDER-36.11; Relay_SPDT_Finder_36.11
M1: Motor_DC; PinHeader_1x02_P2.54mm_Vertical
Q1, Q2, Q3, Q4: IRF3205; TO-220-3_Vertical
R1: 1k; R_Axial_DIN0207_L6.3mm_D2.5mm_P7.62mm_Horizontal
R2, R4, R10: 330; R_Axial_DIN0207_L6.3mm_D2.5mm_P7.62mm_Horizontal
R3: PTC; R_Axial_DIN0204_L3.6mm_D1.6mm_P5.08mm_Horizontal
R5: 100; R_Axial_DIN0207_L6.3mm_D2.5mm_P7.62mm_Horizontal
R6: 10k; R_Axial_DIN0207_L6.3mm_D2.5mm_P7.62mm_Horizontal
R7, R8: 220; R_Axial_DIN0207_L6.3mm_D2.5mm_P7.62mm_Horizontal
R9: 39k; R_Axial_DIN0207_L6.3mm_D2.5mm_P7.62mm_Horizontal
RV1: 100k; Potentiometer_Runtron_RM-065_Vertical
U1: 4047; DIP-14_W7.62mm_LongPads

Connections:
+12P: C2.1, D2.1 (K), D5.2 (A), J7.2, K1.14, M1.1 (+), R1.1, R2.2
+12V: J5.2, J6.1, K1.11, Q2.2 (D)
GNDA: C2.2, D1.1 (K), D3.1 (K), D4.2 (A), J5.1, K1.A2, Q1.3 (S), Q3.3 (S), Q4.3 (S), R3.2, R6.1, U1.7 (VSS), U1.8 (+TRIGGER), U1.9 (EXT_RESET), U1.12 (RETRIGGER)
unnamed: D1.2 (A), R2.1
unnamed: D2.2 (A), M1.2 (-), Q1.2 (D)
unnamed: D3.2 (A), R4.1
unnamed: D4.1 (K), K1.A1, Q2.3 (S)
unnamed: D5.1 (K), R10.2
unnamed: J6.2, R5.2
unnamed: J7.1, Q3.2 (D)
unnamed: J7.3, Q4.2 (D)
unnamed: K1.12, R4.2
unnamed: Q1.1 (G), R1.2, R3.1
unnamed: Q2.1 (G), R5.1, R6.2
unnamed: Q3.1 (G), R7.2
unnamed: Q4.1 (G), R8.2
unnamed: R9.2, RV1.1, RV1.2
unnamed: R10.1, U1.4 (~ASTABLE), U1.5 (ASTABLE), U1.6 (-TRIGGER), U1.14 (VDD)
unnamed: C3.1, U1.1 (C)
unnamed: R7.1, U1.10 (Q)
unnamed: R9.1, U1.2 (R)
unnamed: C3.2, RV1.3, U1.3 (RC_COMMON)
unnamed: R8.1, U1.11 (~Q)

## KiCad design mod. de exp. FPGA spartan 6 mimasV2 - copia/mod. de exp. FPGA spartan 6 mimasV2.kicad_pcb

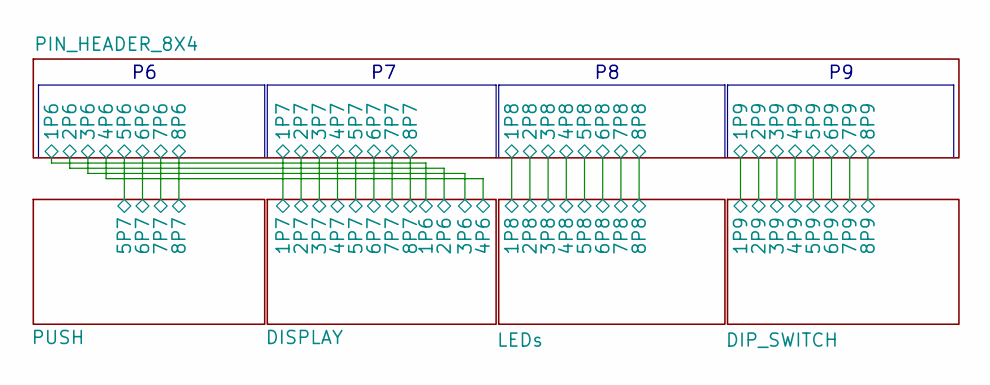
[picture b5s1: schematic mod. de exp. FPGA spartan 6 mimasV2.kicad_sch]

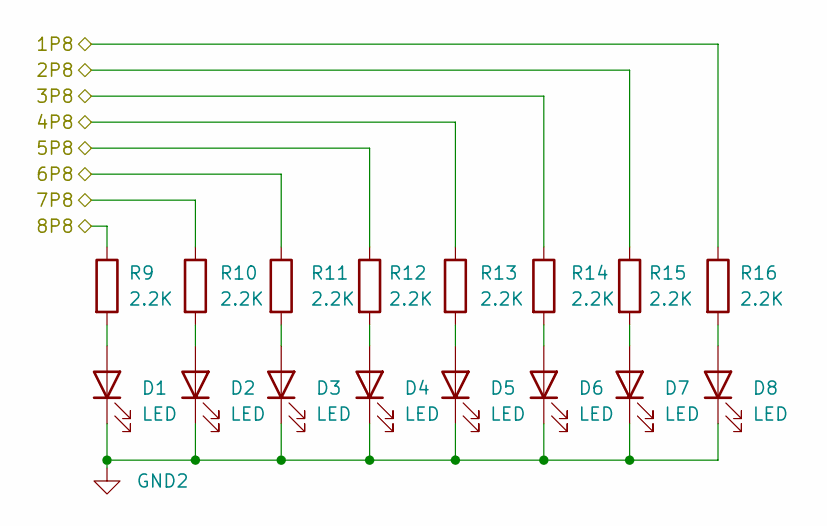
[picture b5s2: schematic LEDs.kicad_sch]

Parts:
D1, D2, D3, D4, D5, D6, D7, D8: LED; LED_D5.0mm
R9, R10, R11, R12, R13, R14, R15, R16: 2.2K; R_Axial_DIN0207_L6.3mm_D2.5mm_P7.62mm_Horizontal

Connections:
/LEDs/1P8: R16.1; also elsewhere on the board
/LEDs/2P8: R15.1; also elsewhere on the board
/LEDs/3P8: R14.1; also elsewhere on the board
/LEDs/4P8: R13.1; also elsewhere on the board
/LEDs/5P8: R12.1; also elsewhere on the board
/LEDs/6P8: R11.1; also elsewhere on the board
/LEDs/7P8: R10.1; also elsewhere on the board
/LEDs/8P8: R9.1; also elsewhere on the board
unnamed: D1.2 (A), R9.2
unnamed: D2.2 (A), R10.2
unnamed: D3.2 (A), R11.2
unnamed: D4.2 (A), R12.2
unnamed: D5.2 (A), R13.2
unnamed: D6.2 (A), R14.2
unnamed: D7.2 (A), R15.2
unnamed: D8.2 (A), R16.2

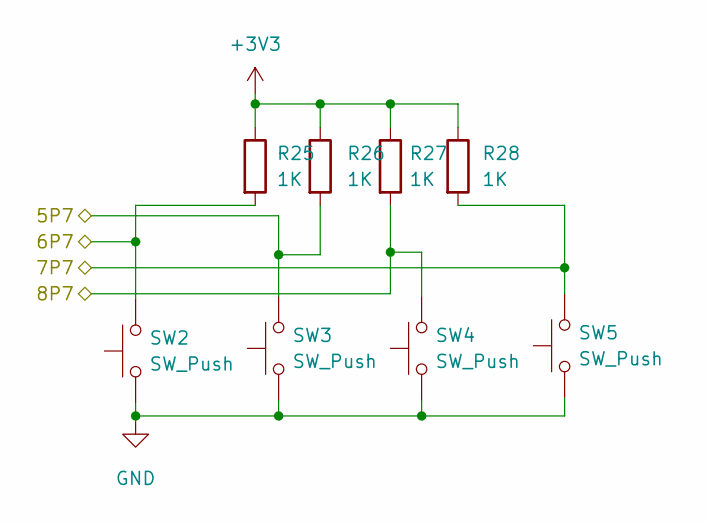
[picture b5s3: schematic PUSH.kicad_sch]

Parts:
R25, R26, R27, R28: 1K; R_Axial_DIN0207_L6.3mm_D2.5mm_P10.16mm_Horizontal
SW2, SW3, SW4, SW5: SW_Push; SW_PUSH_6mm

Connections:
/PIN_HEADER_8X4/5P6: R26.2, SW3.2; also elsewhere on the board
/PIN_HEADER_8X4/6P6: R25.2, SW2.2; also elsewhere on the board
/PIN_HEADER_8X4/7P6: R28.2, SW5.2; also elsewhere on the board
/PIN_HEADER_8X4/8P6: R27.2, SW4.2; also elsewhere on the board
